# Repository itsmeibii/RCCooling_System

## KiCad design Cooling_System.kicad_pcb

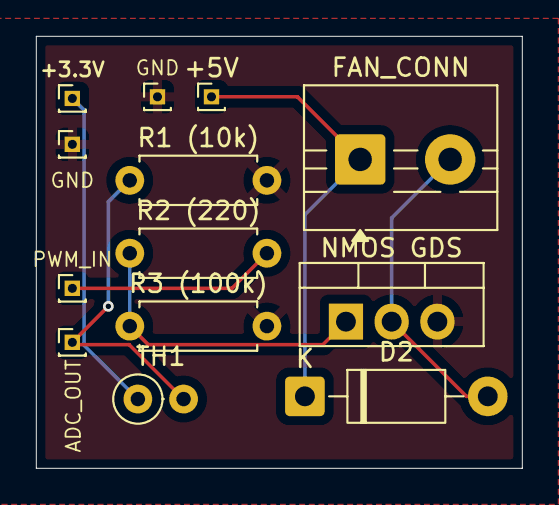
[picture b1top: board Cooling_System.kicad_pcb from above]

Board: 4 copper layers, 27.0 x 24.0 mm, 13 parts (0 on the bottom side), 7 nets.

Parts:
+3.3V, +5V: Conn_01x01_Pin; PinHeader_1x01_P1.00mm_Vertical
ADC_OUT: Conn_01x01_Pin; PinHeader_1x01_P1.00mm_Vertical
D2: D_Schottky; D_DO-41_SOD81_P10.16mm_Horizontal
FAN_CONN: Conn_01x02_Pin; TerminalBlock_MaiXu_MX126-5.0-02P_1x02_P5.00mm
GND: Conn_01x01_Pin; PinHeader_1x01_P1.00mm_Vertical
GND#2: Conn_01x01_Pin; PinHeader_1x01_P1.00mm_Vertical
NMOS GDS: Q_NMOS_GDS; TO-220-3_Vertical
PWM_IN: Conn_01x01_Pin; PinHeader_1x01_P1.00mm_Vertical
R1 (10k): 10k; R_Axial_DIN0207_L6.3mm_D2.5mm_P7.62mm_Horizontal
R2 (220): 220; R_Axial_DIN0207_L6.3mm_D2.5mm_P7.62mm_Horizontal
R3 (100k): 100k; R_Axial_DIN0207_L6.3mm_D2.5mm_P7.62mm_Horizontal
TH1: 10K TH; R_Axial_DIN0207_L6.3mm_D2.5mm_P2.54mm_Vertical

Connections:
/3.3V: +3.3V.1, TH1.1
/5V_IN: +5V.1, D2.1 (K), FAN_CONN.1 (+FAN_IN)
/PWM_IN: PWM_IN.1, R2 (220).2
/TEMP1_ADC: ADC_OUT.1, R1 (10k).1, TH1.2
GND: GND.1, GND#2.1, NMOS GDS.3 (S), R1 (10k).2, R3 (100k).2
unnamed: D2.2 (A), FAN_CONN.2 (-FAN_IN), NMOS GDS.2 (D)
unnamed: NMOS GDS.1 (G), R2 (220).1, R3 (100k).1

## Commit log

2025-11-09 Added some more stuff. Teensy in
2025-11-10 circuit schematic with metric logging output
2026-03-31 Cooling System V1
